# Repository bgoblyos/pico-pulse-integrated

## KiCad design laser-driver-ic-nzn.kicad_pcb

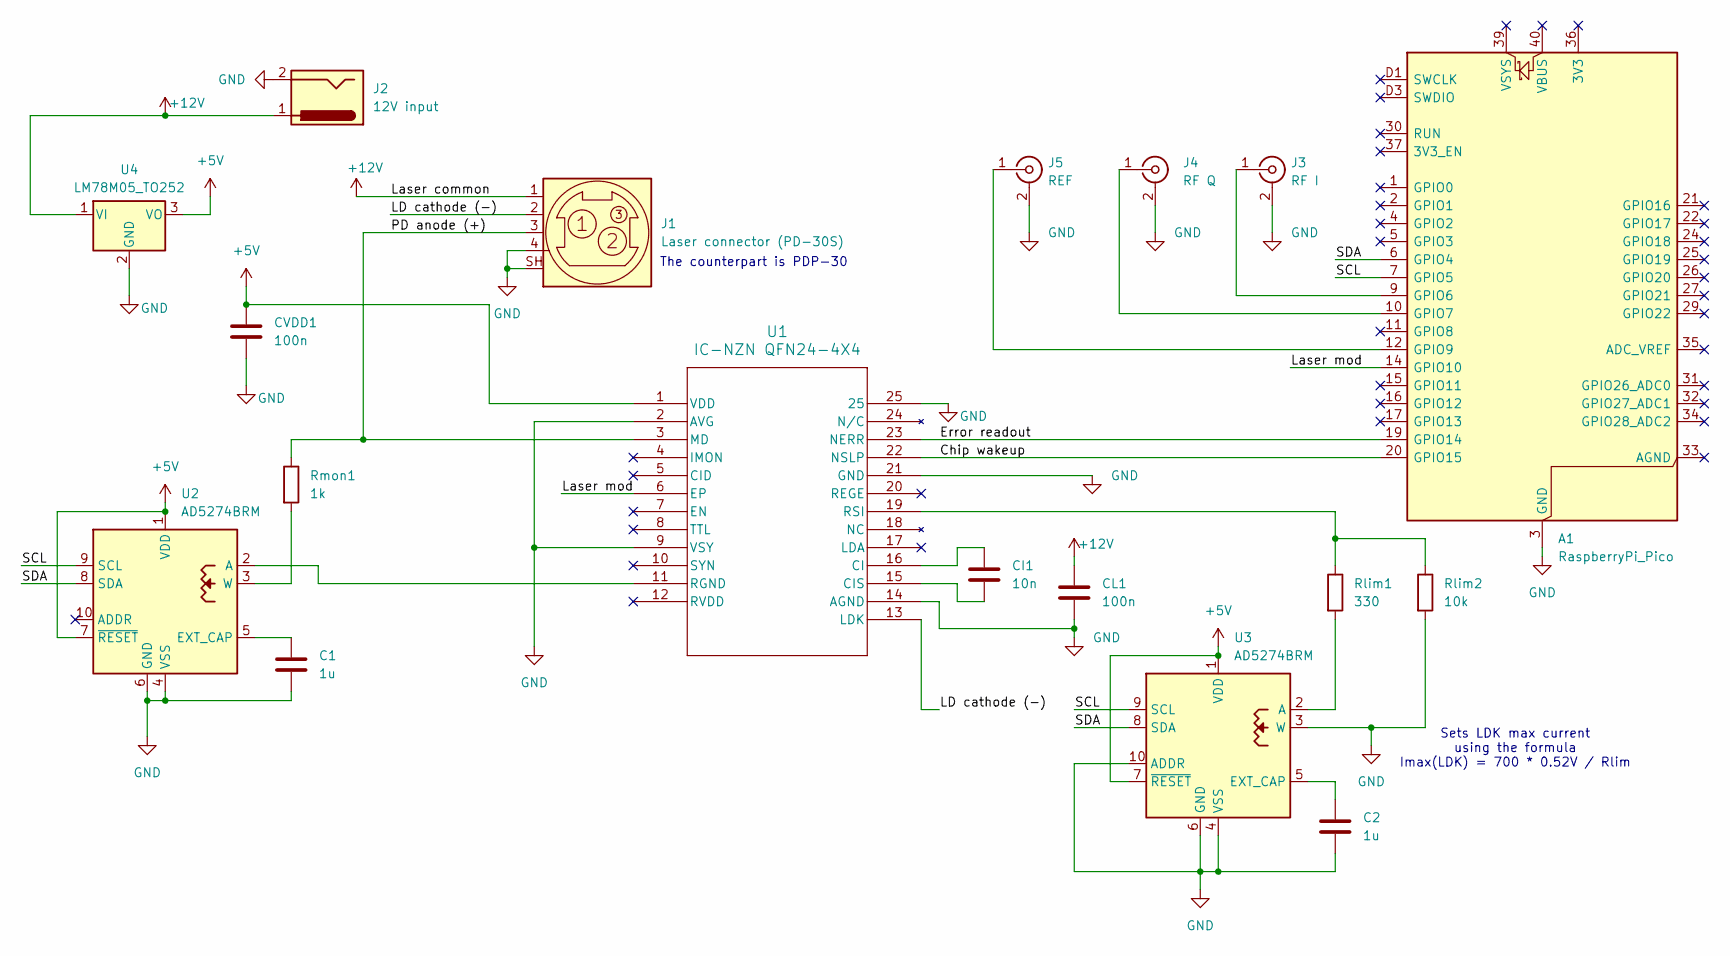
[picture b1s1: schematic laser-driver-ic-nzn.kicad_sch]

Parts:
A1: RaspberryPi_Pico; RaspberryPi_Pico_SMD_HandSolder
C1, C2: 1u; C_0201_0603Metric_Pad0.64x0.40mm_HandSolder
CI1: 10n; C_0201_0603Metric_Pad0.64x0.40mm_HandSolder
CL1: 100n; C_0201_0603Metric_Pad0.64x0.40mm_HandSolder
CVDD1: 100n; C_0201_0603Metric_Pad0.64x0.40mm_HandSolder
J1: Laser connector (PD-30S); CUI_PD-30S
J2: 12V input; BarrelJack_GCT_DCJ200-10-A_Horizontal
J3: RF I; SMA_Amphenol_132289_EdgeMount
J4: RF Q; SMA_Amphenol_132289_EdgeMount
J5: REF; SMA_Amphenol_132289_EdgeMount
Rlim1: 330; R_1206_3216Metric_Pad1.30x1.75mm_HandSolder
Rlim2: 10k; R_1206_3216Metric_Pad1.30x1.75mm_HandSolder
Rmon1: 1k; R_1206_3216Metric_Pad1.30x1.75mm_HandSolder
U1: IC-NZN QFN24-4X4; QFN24-4X4
U2, U3: AD5274BRM; MSOP-10_3x3mm_P0.5mm
U4: LM78M05_TO252; TO-252-2

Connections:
+5V: CVDD1.1, U1.1 (VDD), U2.1 (VDD), U2.7 (~RESET), U3.1 (VDD), U3.7 (~RESET), U4.3 (VO)
+12V: CL1.1, J1.1, J2.1, U4.1 (VI)
/Chip wakeup: A1.20 (GPIO15), U1.22 (NSLP)
/Error readout: A1.19 (GPIO14), U1.23 (NERR)
/LD cathode (-): J1.2, U1.13 (LDK)
/Laser mod: A1.14 (GPIO10), U1.6 (EP)
/PD anode (+): J1.3, Rmon1.1, U1.3 (MD)
/SCL: A1.7 (GPIO5), U2.9 (SCL), U3.9 (SCL)
/SDA: A1.6 (GPIO4), U2.8 (SDA), U3.8 (SDA)
GND: A1.3 (GND), A1.8 (GND), A1.13 (GND), A1.18 (GND), A1.23 (GND), A1.28 (GND), A1.38 (GND), A1.D2 (GND), C1.2, C2.2, CL1.2, CVDD1.2, J1.4 (Shield), J1.SH (Shield), J2.2, J3.2 (Ext), J4.2 (Ext), J5.2 (Ext), Rlim2.2, U1.2 (AVG), U1.9 (VSY), U1.14 (AGND), U1.21 (GND), U1.25, U2.4 (VSS), U2.6 (GND), U3.3 (W), U3.4 (VSS), U3.6 (GND), U3.10 (ADDR), U4.2 (GND)
unnamed: A1.9 (GPIO6), J3.1 (In)
unnamed: A1.10 (GPIO7), J4.1 (In)
unnamed: A1.12 (GPIO9), J5.1 (In)
unnamed: CI1.1, U1.16 (CI)
unnamed: CI1.2, U1.15 (CIS)
unnamed: U1.11 (RGND), U2.2 (A)
unnamed: Rlim1.1, Rlim2.1, U1.19 (RSI)
unnamed: C1.1, U2.5 (EXT_CAP)
unnamed: Rmon1.2, U2.3 (W)
unnamed: Rlim1.2, U3.2 (A)
unnamed: C2.1, U3.5 (EXT_CAP)

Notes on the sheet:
Sets LDK max current using the formula Imax(LDK) = 700 * 0.52V / Rlim
The counterpart is PDP-30

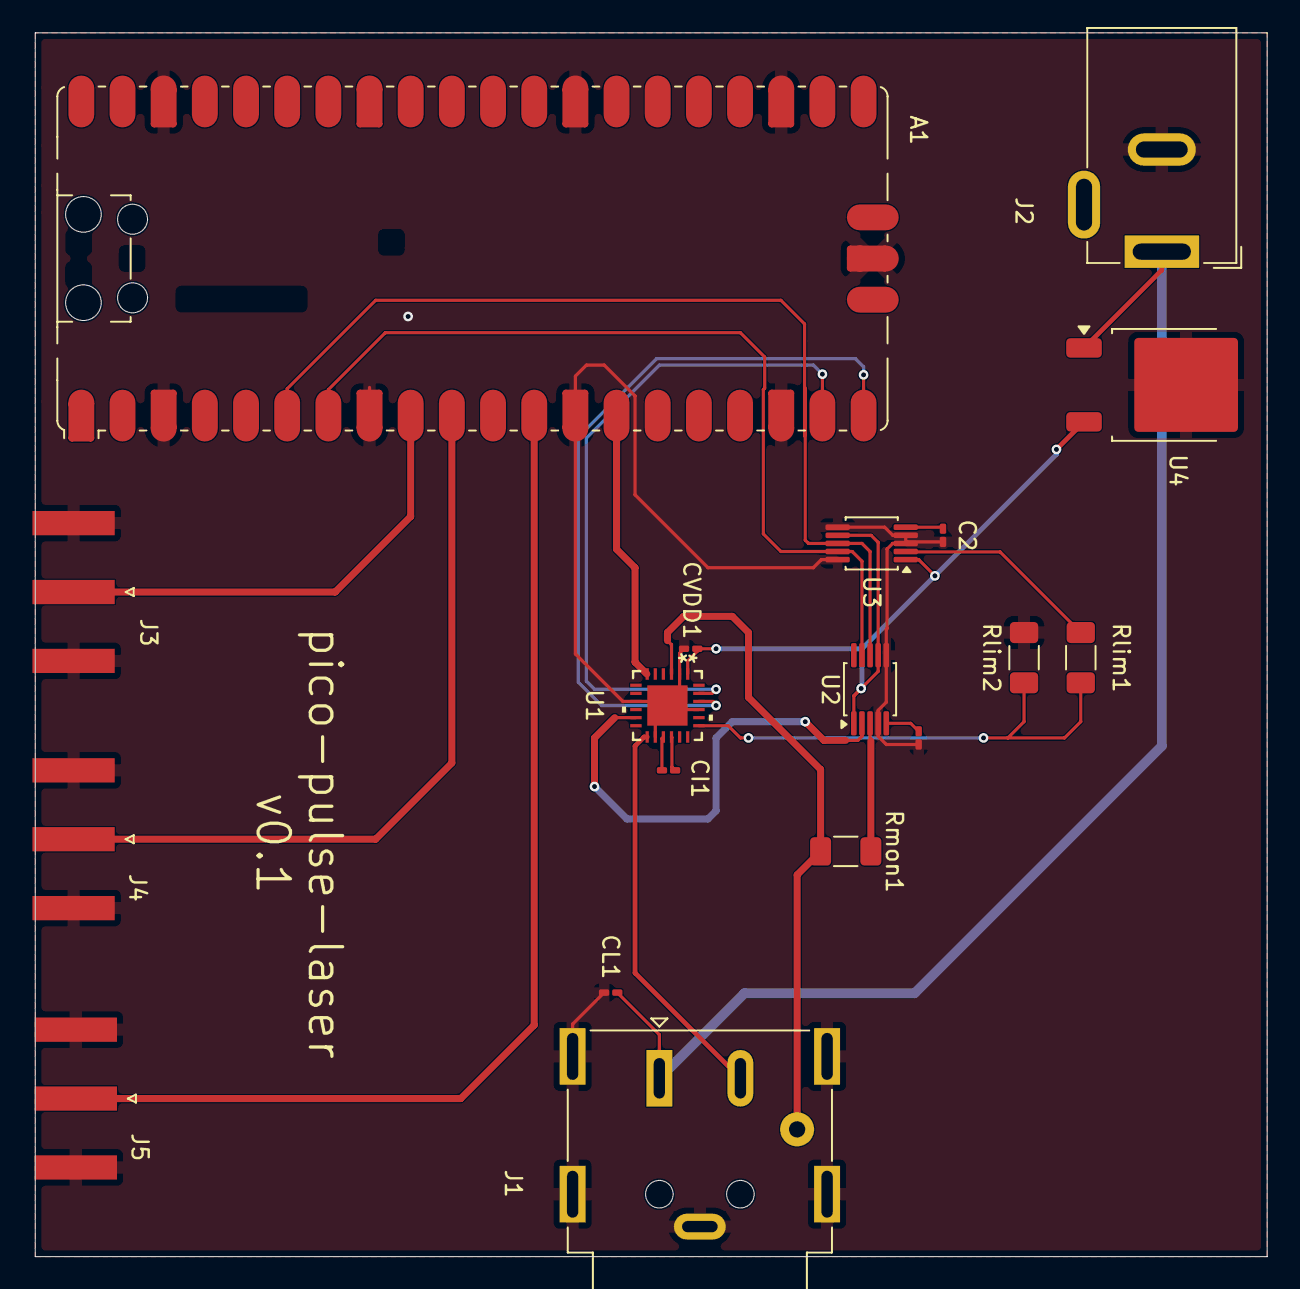
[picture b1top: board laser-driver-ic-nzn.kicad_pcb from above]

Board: 2 copper layers, 76.0 x 75.5 mm, 18 parts (0 on the bottom side), 21 nets.
